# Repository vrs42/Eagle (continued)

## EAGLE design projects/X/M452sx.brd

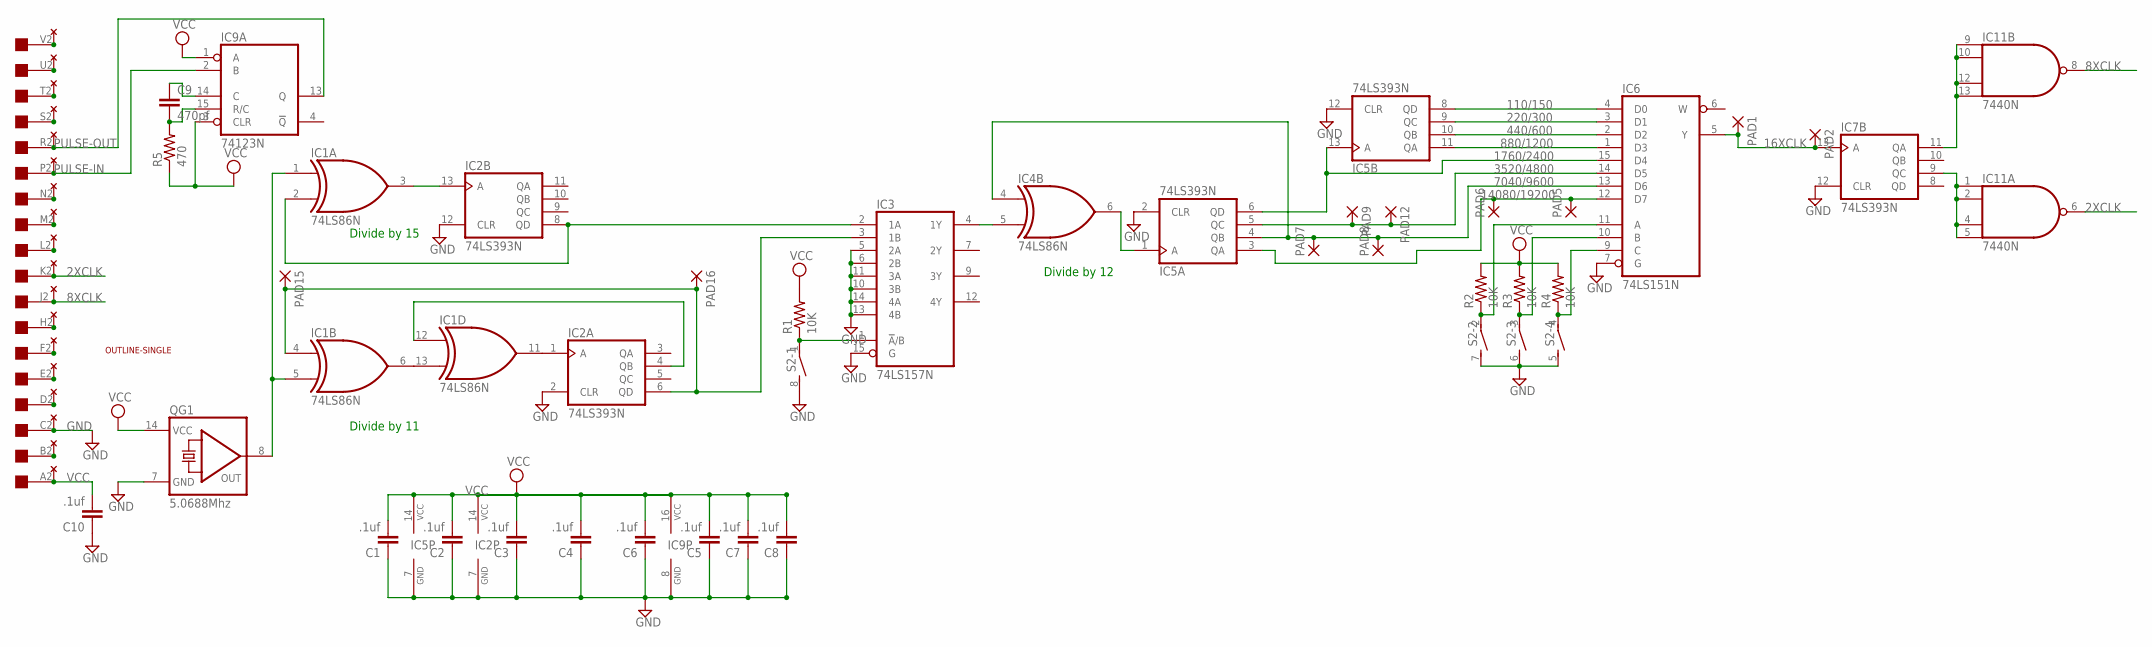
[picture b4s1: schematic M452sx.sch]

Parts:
C1, C2, C3, C4, C5, C6, C7, C8, C10: .1uf; C050-025X075
C9: 470pf; C050-025X075
IC1, IC4: 74LS86N; DIL14
IC2, IC5, IC7: 74LS393N; DIL14
IC3: 74LS157N; DIL16
IC6: 74LS151N; DIL16
IC9: 74123N; DIL16
IC11: 7440N; DIL14
PAD1, PAD2, PAD5, PAD6, PAD7, PAD8, PAD9, PAD12, PAD15, PAD16: 1,6/0,8
QG1: 5.0688Mhz; DIL14S
R1, R2, R3, R4: 10K; 0204/7
R5: 470; 0204/7
S2: DIP04S
U$2: EDGE-1; EDGE-CON1
U$3: THRU-HOLE1
U$4: OUTLINE-SINGLE; SINGLE

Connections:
2XCLK: IC11.6 (O), U$2.K2, U$3.K2
8XCLK: IC11.8 (O), U$2.J2, U$3.J2
16XCLK: IC6.5 (Y), IC7.13 (A), PAD1.1, PAD2.1
110/150: IC5.8 (QD), IC6.4 (D0)
220/300: IC5.9 (QC), IC6.3 (D1)
440/600: IC5.10 (QB), IC6.2 (D2)
880/1200: IC5.11 (QA), IC6.1 (D3)
1760/2400: IC5.6 (QD), IC5.13 (A), IC6.15 (D4)
3520/4800: IC5.5 (QC), IC6.14 (D5), PAD9.1, PAD12.1
7040/9600: IC4.4 (I0), IC5.4 (QB), IC6.13 (D6), PAD7.1, PAD8.1
14080/19200: IC5.3 (QA), IC6.12 (D7), PAD5.1, PAD6.1
GND: C1.1, C2.1, C3.1, C4.1, C5.1, C6.1, C7.1, C8.1, C10.1, IC1.7 (GND), IC2.2 (CLR), IC2.7 (GND), IC2.12 (CLR), IC3.5 (2A), IC3.6 (2B), IC3.8 (GND), IC3.10 (3B), IC3.11 (3A), IC3.13 (4B), IC3.14 (4A), IC3.15 (G), IC4.7 (GND), IC5.2 (CLR), IC5.7 (GND), IC5.12 (CLR), IC6.7 (G), IC6.8 (GND), IC7.7 (GND), IC7.12 (CLR), IC9.8 (GND), IC11.7 (GND), QG1.7 (GND), S2.5 (2), S2.6 (2), S2.7 (2), S2.8 (2), U$2.C2, U$3.C2
unnamed: IC1.1 (I0), IC1.5 (I1), QG1.8 (OUT)
unnamed: IC1.2 (I1), IC2.8 (QD), IC3.2 (1A)
unnamed: IC1.4 (I0), IC2.6 (QD), IC3.3 (1B), PAD15.1, PAD16.1
unnamed: U$2.V2, U$3.V2
unnamed: U$2.U2, U$3.U2
unnamed: IC1.3 (O), IC2.13 (A)
unnamed: IC1.11 (O), IC2.1 (A)
unnamed: IC6.11 (A), R2.1, S2.2 (1)
unnamed: IC3.4 (1Y), IC4.5 (I1)
unnamed: IC7.9 (QC), IC11.1 (I0), IC11.2 (I1), IC11.4 (I2), IC11.5 (I3)
unnamed: IC4.6 (O), IC5.1 (A)
unnamed: IC7.11 (QA), IC11.9 (I0), IC11.10 (I1), IC11.12 (I2), IC11.13 (I3)
unnamed: IC6.10 (B), R3.1, S2.3 (1)
unnamed: IC6.9 (C), R4.1, S2.4 (1)
unnamed: IC1.6 (O), IC1.13 (I1)
unnamed: U$2.T2, U$3.T2
unnamed: IC3.1 (!A!/B), R1.1, S2.1
unnamed: U$2.S2, U$3.S2
unnamed: IC1.12 (I0), IC2.4 (QB)
unnamed: U$2.N2, U$3.N2
unnamed: C9.2, IC9.15 (R/C), R5.2
unnamed: C9.1, IC9.14 (C)
unnamed: U$2.M2, U$3.M2
unnamed: U$2.L2, U$3.L2
unnamed: U$2.H2, U$3.H2
unnamed: U$2.F2, U$3.F2
unnamed: U$2.E2, U$3.E2
unnamed: U$2.D2, U$3.D2
unnamed: U$2.B2, U$3.B2
PULSE-IN: IC9.2 (B), U$2.P2, U$3.P2
PULSE-OUT: IC9.13 (Q), U$2.R2, U$3.R2
VCC: C1.2, C2.2, C3.2, C4.2, C5.2, C6.2, C7.2, C8.2, C10.2, IC1.14 (VCC), IC2.14 (VCC), IC3.16 (VCC), IC4.14 (VCC), IC5.14 (VCC), IC6.16 (VCC), IC7.14 (VCC), IC9.1 (A), IC9.3 (CLR), IC9.16 (VCC), IC11.14 (VCC), QG1.14 (VCC), R1.2, R2.2, R3.2, R4.2, R5.1, U$2.A2, U$3.A2

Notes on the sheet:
Divide by 11
Divide by 15
Divide by 12

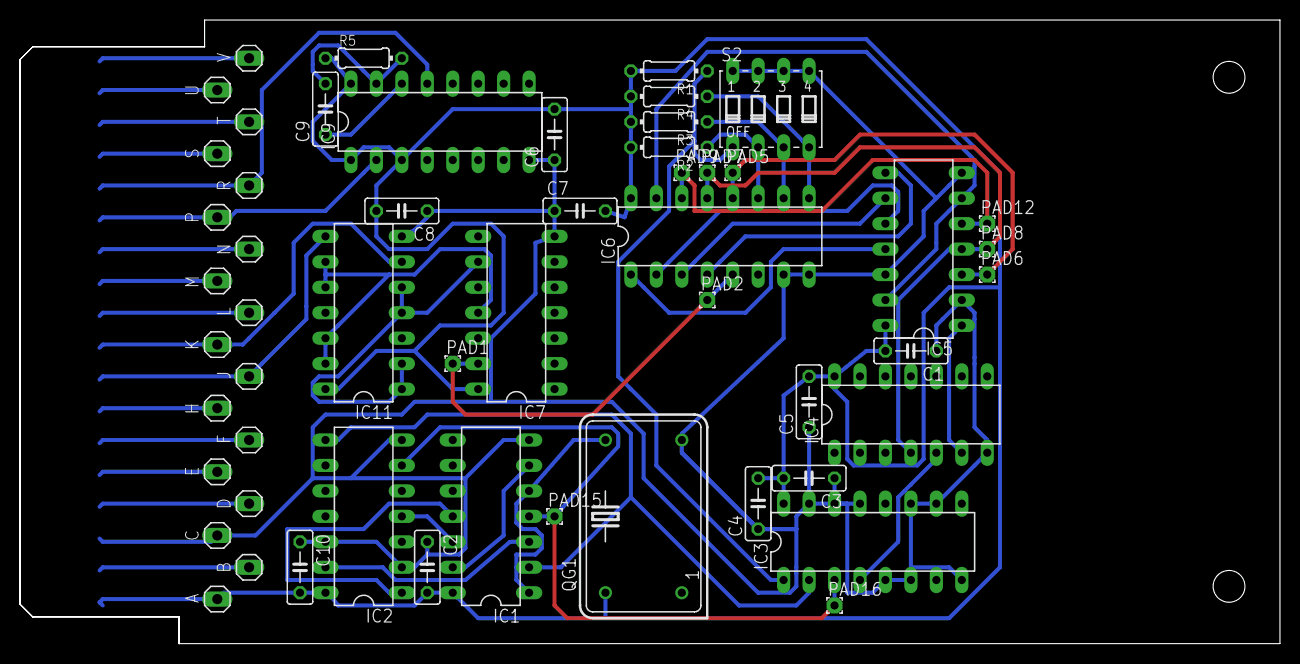
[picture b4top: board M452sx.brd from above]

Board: 2 copper layers, 125.7 x 62.2 mm, 39 parts (0 on the bottom side), 44 nets.

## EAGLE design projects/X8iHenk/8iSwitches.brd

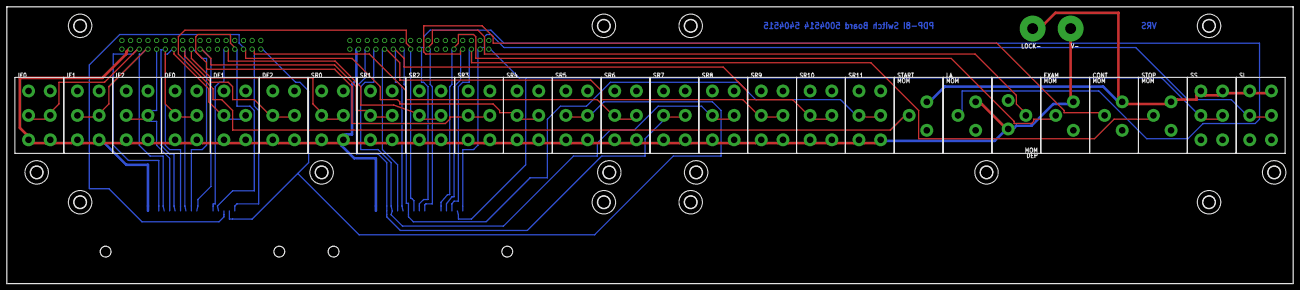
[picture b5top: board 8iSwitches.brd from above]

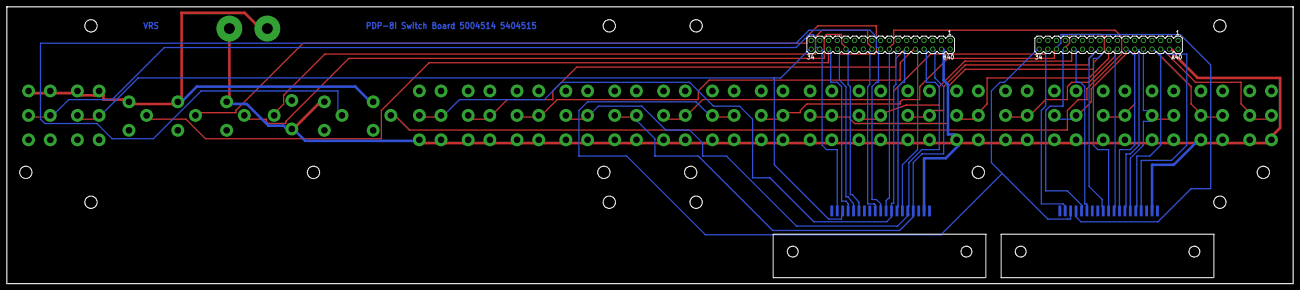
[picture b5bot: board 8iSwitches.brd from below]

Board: 2 copper layers, 376.2 x 81.0 mm, 48 parts (6 on the bottom side), 28 nets.

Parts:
A40: MA17-2
B40: MA17-2
CONT: SPDT8I
DEP: SPDT8I
DF0, DF1, DF2: DPDT8I
EXAM: SPDT8I
FLEXA: FLEX19
FLEXB: FLEX19
IF0, IF1, IF2: DPDT8I
LA: SPDT8I
LOCK-: LUG; SPADELUG
SI: DPDT8I
SR0, SR1, SR2, SR3, SR4, SR5, SR6, SR7, SR8, SR9, SR10, SR11: DPDT8I
SS: DPDT8I
START: SPDT8I
STOP: SPDT8I
U$1, U$2, U$3, U$4, U$5, U$6, U$7, U$10, U$11, U$12, U$13, U$14, U$15, U$16: 3,6
U$17, U$18: STRAIN-RELIEF
V-: LUG; SPADELUG

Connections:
CONT: B40.28, CONT.A2, FLEXB.5
DEP: B40.20, DEP.A2, FLEXB.9
DF0: A40.6, FLEXA.16, IF0.L2, IF0.R2
DF1: A40.8, FLEXA.15, IF1.L2, IF1.R2
DF2: A40.10, FLEXA.14, IF2.L2, IF2.R2
EXAM: B40.26, EXAM.A2, FLEXB.6
IF0: A40.12, DF0.L2, DF0.R2, FLEXA.13
IF1: A40.14, DF1.L2, DF1.R2, FLEXA.12
IF2: A40.16, DF2.L2, DF2.R2, FLEXA.11
LA: B40.18, FLEXB.10, LA.A2
LOCK-: CONT.A1, LOCK-.1, SI.L1, SI.R1, SS.L1, SS.R1, START.A1, STOP.A1
SI: B40.32, FLEXB.2, SI.L2, SI.R2
SR0: A40.18, FLEXA.10, SR0.L2, SR0.R2
SR1: A40.20, FLEXA.9, SR1.L2, SR1.R2
SR2: A40.26, FLEXA.6, SR2.L2, SR2.R2
SR3: A40.28, FLEXA.5, SR3.L2, SR3.R2
SR4: A40.30, FLEXA.4, SR4.L2, SR4.R2
SR5: A40.34, FLEXA.3, SR5.L2, SR5.R2
SR6: A40.32, FLEXA.2, SR6.L2, SR6.R2
SR7: B40.6, FLEXB.16, SR7.L2, SR7.R2
SR8: B40.8, FLEXB.15, SR8.L2, SR8.R2
SR9: B40.10, FLEXB.14, SR9.L2, SR9.R2
SR10: B40.12, FLEXB.13, SR10.L2, SR10.R2
SR11: B40.14, FLEXB.12, SR11.L2, SR11.R2
SS: B40.34, FLEXB.3, SS.L2, SS.R2
START: B40.16, FLEXB.11, START.A2
STOP: B40.30, FLEXB.4, STOP.A2
V-: A40.4, B40.4, DEP.A1, DF0.L3, DF0.R3, DF1.L3, DF1.R3, DF2.L3, DF2.R3, EXAM.A1, FLEXA.18, FLEXB.18, IF0.L3, IF0.R3, IF1.L3, IF1.R3, IF2.L3, IF2.R3, LA.A1, SR0.L3, SR0.R3, SR1.L3, SR1.R3, SR2.L3, SR2.R3, SR3.L3, SR3.R3, SR4.L3, SR4.R3, SR5.L3, SR5.R3, SR6.L3, SR6.R3, SR7.L3, SR7.R3, SR8.L3, SR8.R3, SR9.L3, SR9.R3, SR10.L3, SR10.R3, SR11.L3, SR11.R3, V-.1

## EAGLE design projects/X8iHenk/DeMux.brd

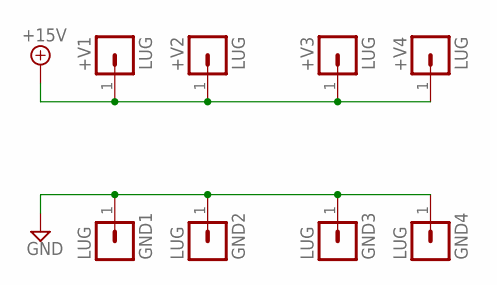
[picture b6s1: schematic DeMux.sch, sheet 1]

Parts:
+V1, +V2, +V3, +V4: LUG; SPADELUG
GND1, GND2, GND3, GND4: LUG; SPADELUG

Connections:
+15V: +V1.1, +V2.1, +V3.1, +V4.1
GND: GND1.1, GND2.1, GND3.1, GND4.1; also elsewhere on the board

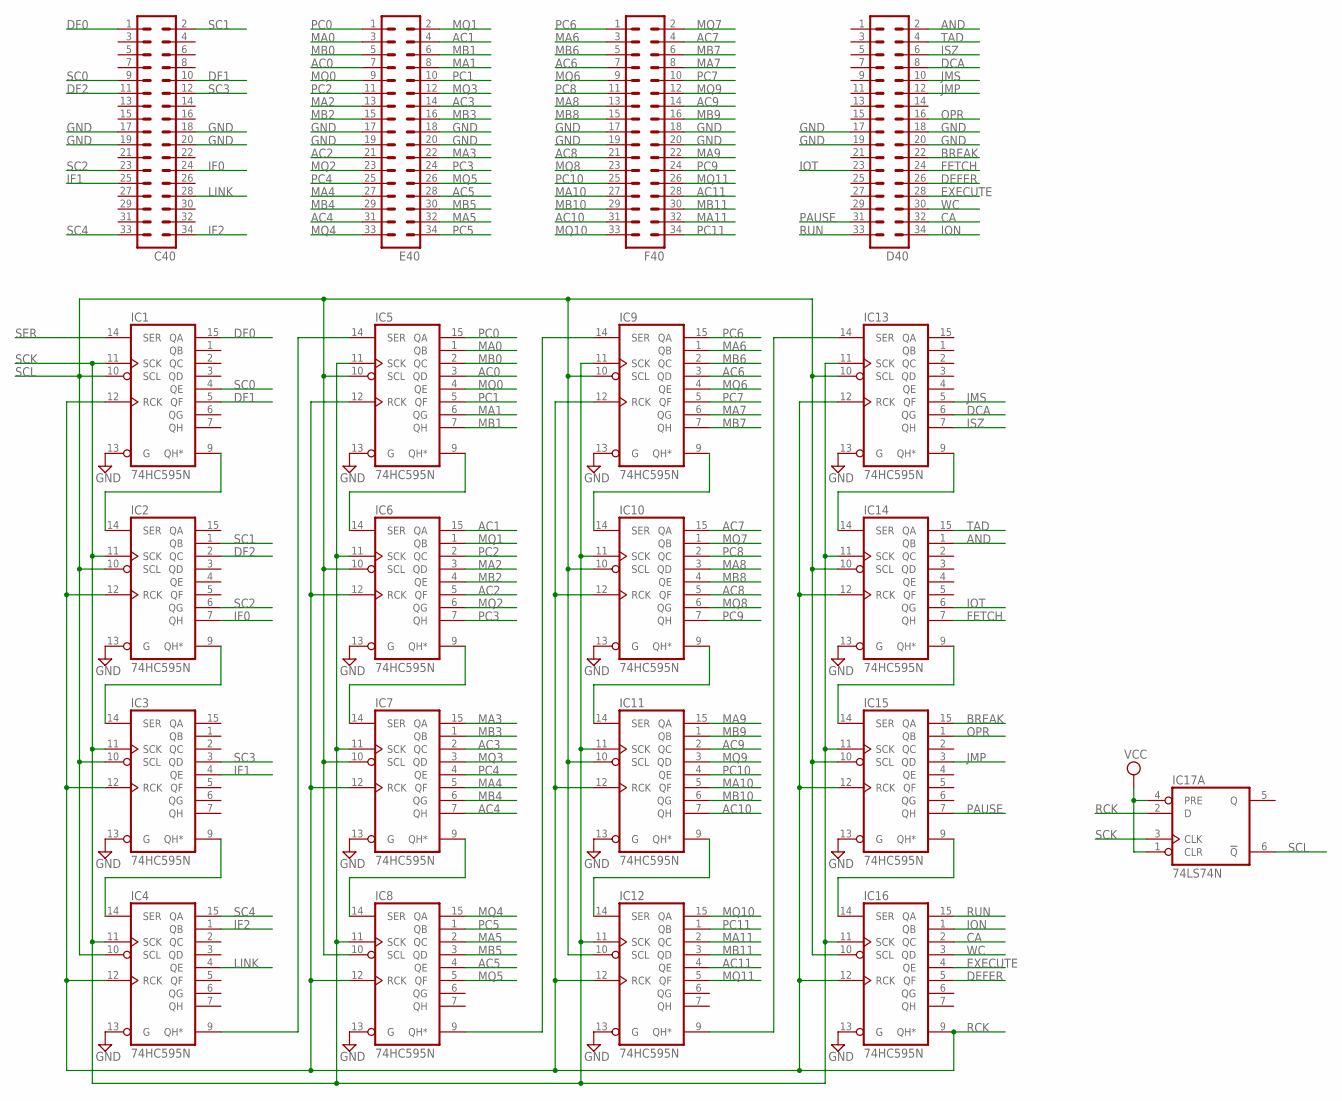
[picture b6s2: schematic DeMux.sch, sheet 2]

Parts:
C40: MA17-2
D40: MA17-2
E40: MA17-2
F40: MA17-2
IC1, IC2, IC3, IC4, IC5, IC6, IC7, IC8, IC9, IC10, IC11, IC12, IC13, IC14, IC15, IC16: 74HC595N; DIL16
IC17: 74LS74N; DIL14

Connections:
AC0: E40.7, IC5.3 (QD)
AC1: E40.4, IC6.15 (QA)
AC2: E40.21, IC6.5 (QF)
AC3: E40.14, IC7.2 (QC)
AC4: E40.31, IC7.7 (QH)
AC5: E40.28, IC8.4 (QE)
AC6: F40.7, IC9.3 (QD)
AC7: F40.4, IC10.15 (QA)
AC8: F40.21, IC10.5 (QF)
AC9: F40.14, IC11.2 (QC)
AC10: F40.31, IC11.7 (QH)
AC11: F40.28, IC12.4 (QE)
AND: D40.2, IC14.1 (QB)
BREAK: D40.22, IC15.15 (QA)
CA: D40.32, IC16.2 (QC)
DCA: D40.8, IC13.6 (QG)
DEFER: D40.26, IC16.5 (QF)
DF0: C40.1, IC1.15 (QA)
DF1: C40.10, IC1.5 (QF)
DF2: C40.11, IC2.2 (QC)
EXECUTE: D40.28, IC16.4 (QE)
FETCH: D40.24, IC14.7 (QH)
GND: C40.17, C40.18, C40.19, C40.20, D40.17, D40.18, D40.19, D40.20, E40.17, E40.18, E40.19, E40.20, F40.17, F40.18, F40.19, F40.20, IC1.8 (GND), IC1.13 (G), IC2.8 (GND), IC2.13 (G), IC3.8 (GND), IC3.13 (G), IC4.8 (GND), IC4.13 (G), IC5.8 (GND), IC5.13 (G), IC6.8 (GND), IC6.13 (G), IC7.8 (GND), IC7.13 (G), IC8.8 (GND), IC8.13 (G), IC9.8 (GND), IC9.13 (G), IC10.8 (GND), IC10.13 (G), IC11.8 (GND), IC11.13 (G), IC12.8 (GND), IC12.13 (G), IC13.8 (GND), IC13.13 (G), IC14.8 (GND), IC14.13 (G), IC15.8 (GND), IC15.13 (G), IC16.8 (GND), IC16.13 (G), IC17.7 (GND); also elsewhere on the board
IF0: C40.24, IC2.7 (QH)
IF1: C40.25, IC3.4 (QE)
IF2: C40.34, IC4.1 (QB)
ION: D40.34, IC16.1 (QB)
IOT: D40.23, IC14.6 (QG)
ISZ: D40.6, IC13.7 (QH)
JMP: D40.12, IC15.3 (QD)
JMS: D40.10, IC13.5 (QF)
LINK: C40.28, IC4.4 (QE)
MA0: E40.3, IC5.1 (QB)
MA1: E40.8, IC5.6 (QG)
MA2: E40.13, IC6.3 (QD)
MA3: E40.22, IC7.15 (QA)
MA4: E40.27, IC7.5 (QF)
MA5: E40.32, IC8.2 (QC)
MA6: F40.3, IC9.1 (QB)
MA7: F40.8, IC9.6 (QG)
MA8: F40.13, IC10.3 (QD)
MA9: F40.22, IC11.15 (QA)
MA10: F40.27, IC11.5 (QF)
MA11: F40.32, IC12.2 (QC)
MB0: E40.5, IC5.2 (QC)
MB1: E40.6, IC5.7 (QH)
MB2: E40.15, IC6.4 (QE)
MB3: E40.16, IC7.1 (QB)
MB4: E40.29, IC7.6 (QG)
MB5: E40.30, IC8.3 (QD)
MB6: F40.5, IC9.2 (QC)
MB7: F40.6, IC9.7 (QH)
MB8: F40.15, IC10.4 (QE)
MB9: F40.16, IC11.1 (QB)
MB10: F40.29, IC11.6 (QG)
MB11: F40.30, IC12.3 (QD)
MQ0: E40.9, IC5.4 (QE)
MQ1: E40.2, IC6.1 (QB)
MQ2: E40.23, IC6.6 (QG)
MQ3: E40.12, IC7.3 (QD)
MQ4: E40.33, IC8.15 (QA)
MQ5: E40.26, IC8.5 (QF)
MQ6: F40.9, IC9.4 (QE)
MQ7: F40.2, IC10.1 (QB)
MQ8: F40.23, IC10.6 (QG)
MQ9: F40.12, IC11.3 (QD)
MQ10: F40.33, IC12.15 (QA)
MQ11: F40.26, IC12.5 (QF)
unnamed: IC5.9 (QH*), IC6.14 (SER)
unnamed: IC1.9 (QH*), IC2.14 (SER)
unnamed: IC2.9 (QH*), IC3.14 (SER)
unnamed: IC3.9 (QH*), IC4.14 (SER)
unnamed: IC7.9 (QH*), IC8.14 (SER)
unnamed: IC6.9 (QH*), IC7.14 (SER)
unnamed: IC11.9 (QH*), IC12.14 (SER)
unnamed: IC10.9 (QH*), IC11.14 (SER)
unnamed: IC14.9 (QH*), IC15.14 (SER)
unnamed: IC15.9 (QH*), IC16.14 (SER)
unnamed: IC9.9 (QH*), IC10.14 (SER)
unnamed: IC13.9 (QH*), IC14.14 (SER)
unnamed: IC4.9 (QH*), IC5.14 (SER)
unnamed: IC8.9 (QH*), IC9.14 (SER)
unnamed: IC12.9 (QH*), IC13.14 (SER)
OPR: D40.16, IC15.1 (QB)
PAUSE: D40.31, IC15.7 (QH)
PC0: E40.1, IC5.15 (QA)
PC1: E40.10, IC5.5 (QF)
PC2: E40.11, IC6.2 (QC)
PC3: E40.24, IC6.7 (QH)
PC4: E40.25, IC7.4 (QE)
PC5: E40.34, IC8.1 (QB)
PC6: F40.1, IC9.15 (QA)
PC7: F40.10, IC9.5 (QF)
PC8: F40.11, IC10.2 (QC)
PC9: F40.24, IC10.7 (QH)
PC10: F40.25, IC11.4 (QE)
PC11: F40.34, IC12.1 (QB)
RCK: IC1.12 (RCK), IC2.12 (RCK), IC3.12 (RCK), IC4.12 (RCK), IC5.12 (RCK), IC6.12 (RCK), IC7.12 (RCK), IC8.12 (RCK), IC9.12 (RCK), IC10.12 (RCK), IC11.12 (RCK), IC12.12 (RCK), IC13.12 (RCK), IC14.12 (RCK), IC15.12 (RCK), IC16.9 (QH*), IC16.12 (RCK), IC17.2 (D)
RUN: D40.33, IC16.15 (QA)
SC0: C40.9, IC1.4 (QE)
SC1: C40.2, IC2.1 (QB)
SC2: C40.23, IC2.6 (QG)
SC3: C40.12, IC3.3 (QD)
SC4: C40.33, IC4.15 (QA)
SCK: IC1.11 (SCK), IC2.11 (SCK), IC3.11 (SCK), IC4.11 (SCK), IC5.11 (SCK), IC6.11 (SCK), IC7.11 (SCK), IC8.11 (SCK), IC9.11 (SCK), IC10.11 (SCK), IC11.11 (SCK), IC12.11 (SCK), IC13.11 (SCK), IC14.11 (SCK), IC15.11 (SCK), IC16.11 (SCK), IC17.3 (CLK)
SCL: IC1.10 (SCL), IC2.10 (SCL), IC3.10 (SCL), IC4.10 (SCL), IC5.10 (SCL), IC6.10 (SCL), IC7.10 (SCL), IC8.10 (SCL), IC9.10 (SCL), IC10.10 (SCL), IC11.10 (SCL), IC12.10 (SCL), IC13.10 (SCL), IC14.10 (SCL), IC15.10 (SCL), IC16.10 (SCL), IC17.6 (!Q)
SER: IC1.14 (SER)
TAD: D40.4, IC14.15 (QA)
VCC: IC1.16 (VCC), IC2.16 (VCC), IC3.16 (VCC), IC4.16 (VCC), IC5.16 (VCC), IC6.16 (VCC), IC7.16 (VCC), IC8.16 (VCC), IC9.16 (VCC), IC10.16 (VCC), IC11.16 (VCC), IC12.16 (VCC), IC13.16 (VCC), IC14.16 (VCC), IC15.16 (VCC), IC16.16 (VCC), IC17.1 (CLR), IC17.4 (PRE), IC17.14 (VCC)
WC: D40.30, IC16.3 (QD)

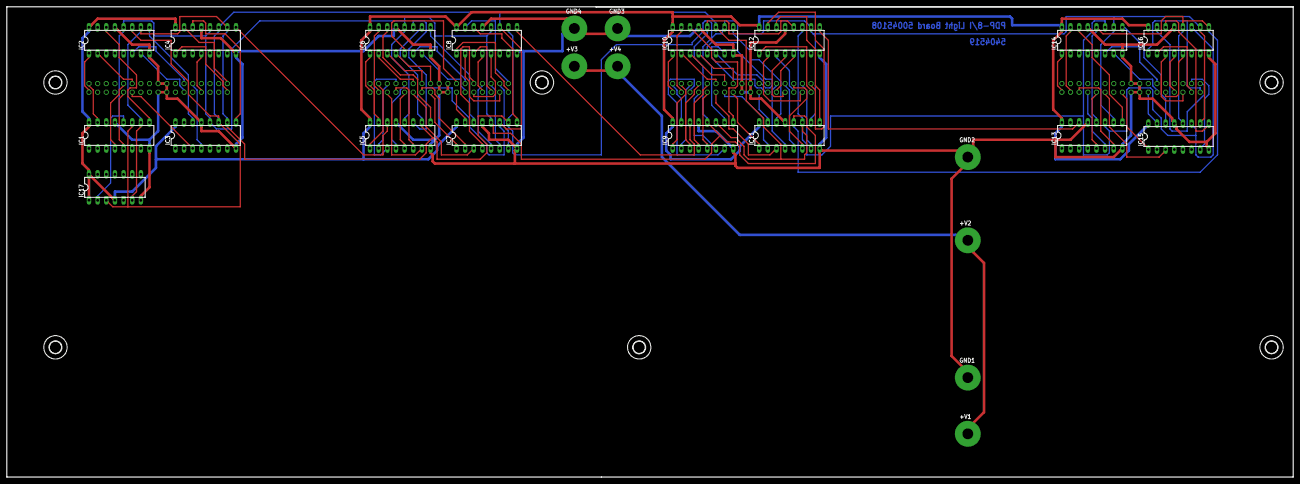
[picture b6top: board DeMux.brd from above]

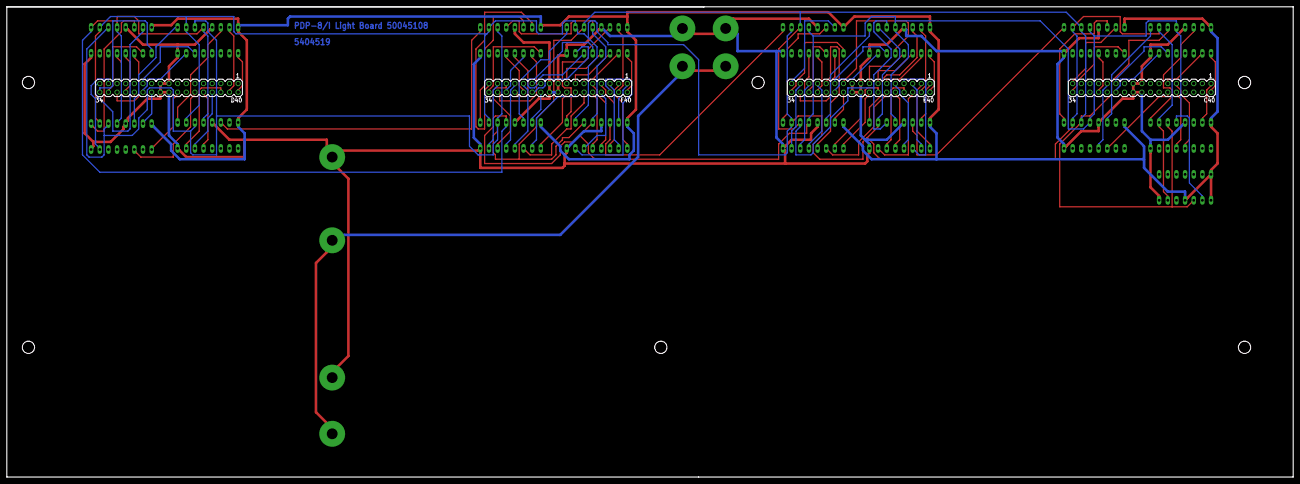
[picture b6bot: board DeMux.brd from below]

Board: 2 copper layers, 377.8 x 138.1 mm, 35 parts (4 on the bottom side), 110 nets.

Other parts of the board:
U$5, U$6, U$7, U$8, U$9, U$11: 3,6

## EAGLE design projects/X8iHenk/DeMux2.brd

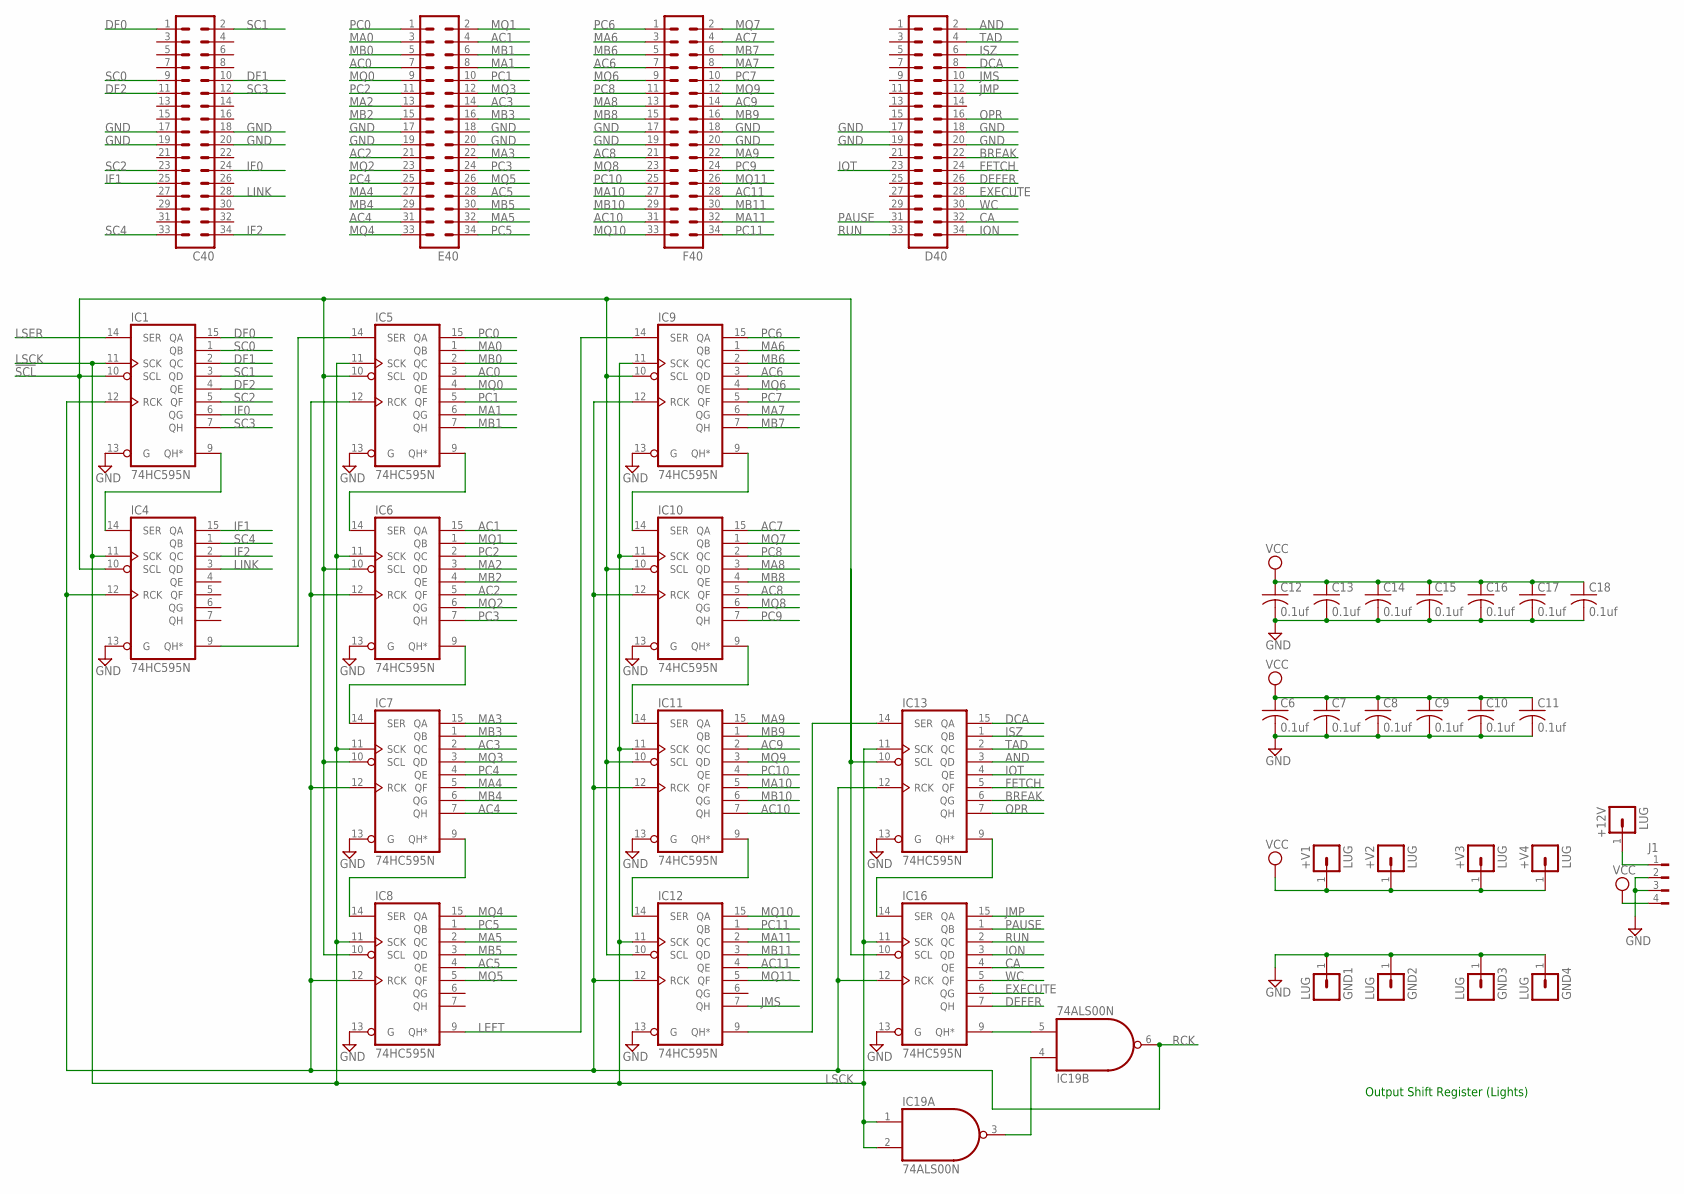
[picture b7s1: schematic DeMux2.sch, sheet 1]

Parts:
+12V: LUG; SPADELUG
+V1, +V2, +V3, +V4: LUG; SPADELUG
C6, C7, C8, C9, C10, C11, C12, C13, C14, C15, C16, C17, C18: 0.1uf; C050-025X075
C40: MA17-2
D40: MA17-2
E40: MA17-2
F40: MA17-2
GND1, GND2, GND3, GND4: LUG; SPADELUG
IC1, IC4, IC5, IC6, IC7, IC8, IC9, IC10, IC11, IC12, IC13, IC16: 74HC595N; DIL16
IC19: 74ALS00N; DIL14
J1: FLOPPY-4

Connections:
!SCL: IC1.10 (SCL), IC4.10 (SCL), IC5.10 (SCL), IC6.10 (SCL), IC7.10 (SCL), IC8.10 (SCL), IC9.10 (SCL), IC10.10 (SCL), IC11.10 (SCL), IC12.10 (SCL), IC13.10 (SCL), IC16.10 (SCL); also elsewhere on the board
+12V: +12V.1, J1.1
AC0: E40.7, IC5.3 (QD)
AC1: E40.4, IC6.15 (QA)
AC2: E40.21, IC6.5 (QF)
AC3: E40.14, IC7.2 (QC)
AC4: E40.31, IC7.7 (QH)
AC5: E40.28, IC8.4 (QE)
AC6: F40.7, IC9.3 (QD)
AC7: F40.4, IC10.15 (QA)
AC8: F40.21, IC10.5 (QF)
AC9: F40.14, IC11.2 (QC)
AC10: F40.31, IC11.7 (QH)
AC11: F40.28, IC12.4 (QE)
AND: D40.2, IC13.3 (QD)
BREAK: D40.22, IC13.6 (QG)
CA: D40.32, IC16.4 (QE)
DCA: D40.8, IC13.15 (QA)
DEFER: D40.26, IC16.7 (QH)
DF0: C40.1, IC1.15 (QA)
DF1: C40.10, IC1.2 (QC)
DF2: C40.11, IC1.4 (QE)
EXECUTE: D40.28, IC16.6 (QG)
FETCH: D40.24, IC13.5 (QF)
GND: C6.2, C7.2, C8.2, C9.2, C10.2, C11.2, C12.2, C13.2, C14.2, C15.2, C16.2, C17.2, C18.2, C40.17, C40.18, C40.19, C40.20, D40.17, D40.18, D40.19, D40.20, E40.17, E40.18, E40.19, E40.20, F40.17, F40.18, F40.19, F40.20, GND1.1, GND2.1, GND3.1, GND4.1, IC1.8 (GND), IC1.13 (G), IC4.8 (GND), IC4.13 (G), IC5.8 (GND), IC5.13 (G), IC6.8 (GND), IC6.13 (G), IC7.8 (GND), IC7.13 (G), IC8.8 (GND), IC8.13 (G), IC9.8 (GND), IC9.13 (G), IC10.8 (GND), IC10.13 (G), IC11.8 (GND), IC11.13 (G), IC12.8 (GND), IC12.13 (G), IC13.8 (GND), IC13.13 (G), IC16.8 (GND), IC16.13 (G), IC19.7 (GND), J1.2, J1.3; also elsewhere on the board
IF0: C40.24, IC1.6 (QG)
IF1: C40.25, IC4.15 (QA)
IF2: C40.34, IC4.2 (QC)
ION: D40.34, IC16.3 (QD)
IOT: D40.23, IC13.4 (QE)
ISZ: D40.6, IC13.1 (QB)
JMP: D40.12, IC16.15 (QA)
JMS: D40.10, IC12.7 (QH)
LEFT: IC8.9 (QH*), IC9.14 (SER); also elsewhere on the board
LINK: C40.28, IC4.3 (QD)
LSCK: IC1.11 (SCK), IC4.11 (SCK), IC5.11 (SCK), IC6.11 (SCK), IC7.11 (SCK), IC8.11 (SCK), IC9.11 (SCK), IC10.11 (SCK), IC11.11 (SCK), IC12.11 (SCK), IC13.11 (SCK), IC16.11 (SCK), IC19.1 (I0), IC19.2 (I1); also elsewhere on the board
LSER: IC1.14 (SER); also elsewhere on the board
MA0: E40.3, IC5.1 (QB)
MA1: E40.8, IC5.6 (QG)
MA2: E40.13, IC6.3 (QD)
MA3: E40.22, IC7.15 (QA)
MA4: E40.27, IC7.5 (QF)
MA5: E40.32, IC8.2 (QC)
MA6: F40.3, IC9.1 (QB)
MA7: F40.8, IC9.6 (QG)
MA8: F40.13, IC10.3 (QD)
MA9: F40.22, IC11.15 (QA)
MA10: F40.27, IC11.5 (QF)
MA11: F40.32, IC12.2 (QC)
MB0: E40.5, IC5.2 (QC)
MB1: E40.6, IC5.7 (QH)
MB2: E40.15, IC6.4 (QE)
MB3: E40.16, IC7.1 (QB)
MB4: E40.29, IC7.6 (QG)
MB5: E40.30, IC8.3 (QD)
MB6: F40.5, IC9.2 (QC)
MB7: F40.6, IC9.7 (QH)
MB8: F40.15, IC10.4 (QE)
MB9: F40.16, IC11.1 (QB)
MB10: F40.29, IC11.6 (QG)
MB11: F40.30, IC12.3 (QD)
MQ0: E40.9, IC5.4 (QE)
MQ1: E40.2, IC6.1 (QB)
MQ2: E40.23, IC6.6 (QG)
MQ3: E40.12, IC7.3 (QD)
MQ4: E40.33, IC8.15 (QA)
MQ5: E40.26, IC8.5 (QF)
MQ6: F40.9, IC9.4 (QE)
MQ7: F40.2, IC10.1 (QB)
MQ8: F40.23, IC10.6 (QG)
MQ9: F40.12, IC11.3 (QD)
MQ10: F40.33, IC12.15 (QA)
MQ11: F40.26, IC12.5 (QF)
unnamed: IC5.9 (QH*), IC6.14 (SER)
unnamed: IC1.9 (QH*), IC4.14 (SER)
unnamed: IC7.9 (QH*), IC8.14 (SER)
unnamed: IC6.9 (QH*), IC7.14 (SER)
unnamed: IC11.9 (QH*), IC12.14 (SER)
unnamed: IC10.9 (QH*), IC11.14 (SER)
unnamed: IC13.9 (QH*), IC16.14 (SER)
unnamed: IC9.9 (QH*), IC10.14 (SER)
unnamed: IC4.9 (QH*), IC5.14 (SER)
unnamed: IC16.9 (QH*), IC19.5 (I1)
unnamed: IC12.9 (QH*), IC13.14 (SER)
unnamed: IC19.3 (O), IC19.4 (I0)
OPR: D40.16, IC13.7 (QH)
PAUSE: D40.31, IC16.1 (QB)
PC0: E40.1, IC5.15 (QA)
PC1: E40.10, IC5.5 (QF)
PC2: E40.11, IC6.2 (QC)
PC3: E40.24, IC6.7 (QH)
PC4: E40.25, IC7.4 (QE)
PC5: E40.34, IC8.1 (QB)
PC6: F40.1, IC9.15 (QA)
PC7: F40.10, IC9.5 (QF)
PC8: F40.11, IC10.2 (QC)
PC9: F40.24, IC10.7 (QH)
PC10: F40.25, IC11.4 (QE)
PC11: F40.34, IC12.1 (QB)
RCK: IC1.12 (RCK), IC4.12 (RCK), IC5.12 (RCK), IC6.12 (RCK), IC7.12 (RCK), IC8.12 (RCK), IC9.12 (RCK), IC10.12 (RCK), IC11.12 (RCK), IC12.12 (RCK), IC13.12 (RCK), IC16.12 (RCK), IC19.6 (O); also elsewhere on the board
RUN: D40.33, IC16.2 (QC)
SC0: C40.9, IC1.1 (QB)
SC1: C40.2, IC1.3 (QD)
SC2: C40.23, IC1.5 (QF)
SC3: C40.12, IC1.7 (QH)
SC4: C40.33, IC4.1 (QB)
TAD: D40.4, IC13.2 (QC)
VCC: +V1.1, +V2.1, +V3.1, +V4.1, C6.1, C7.1, C8.1, C9.1, C10.1, C11.1, C12.1, C13.1, C14.1, C15.1, C16.1, C17.1, C18.1, IC1.16 (VCC), IC4.16 (VCC), IC5.16 (VCC), IC6.16 (VCC), IC7.16 (VCC), IC8.16 (VCC), IC9.16 (VCC), IC10.16 (VCC), IC11.16 (VCC), IC12.16 (VCC), IC13.16 (VCC), IC16.16 (VCC), IC19.14 (VCC), J1.4; also elsewhere on the board
WC: D40.30, IC16.5 (QF)

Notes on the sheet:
Output Shift Register (Lights)

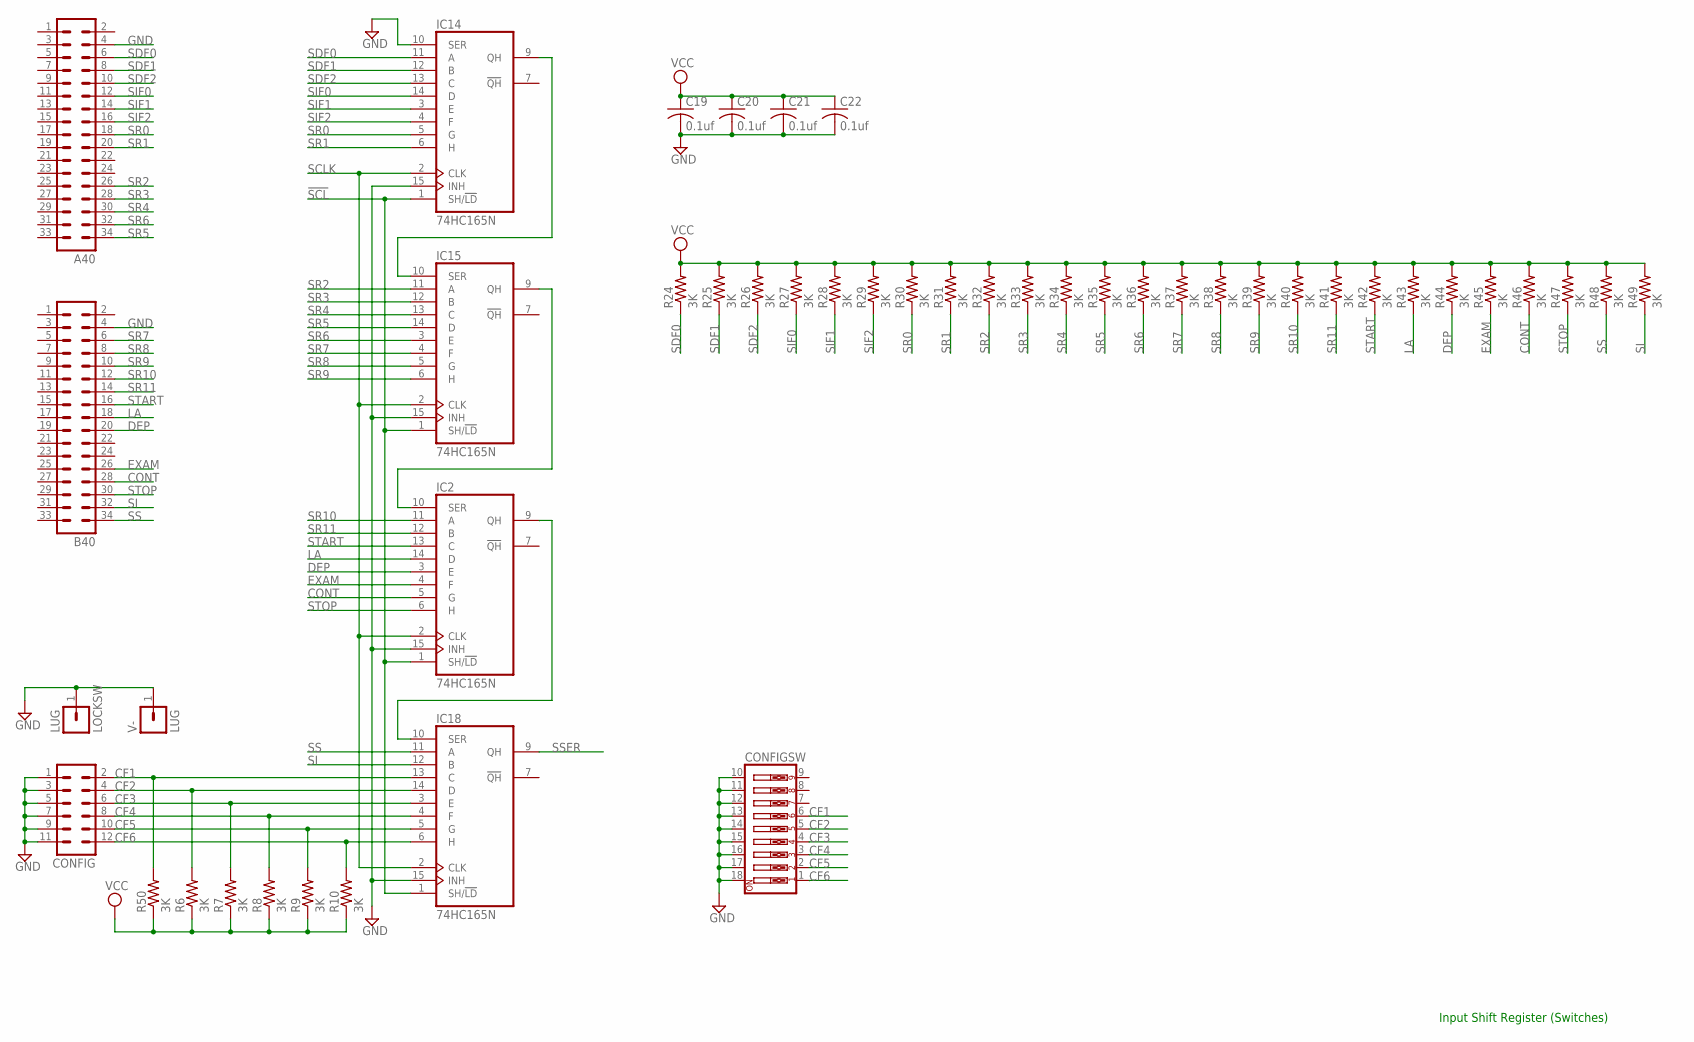
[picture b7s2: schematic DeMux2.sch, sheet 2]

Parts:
A40: MA17-2
B40: MA17-2
C19, C20, C21, C22: 0.1uf; C050-025X075
CONFIG: MA06-2
CONFIGSW: SW_DIP-9; EDG-09
IC2, IC14, IC15, IC18: 74HC165N; DIL16
LOCKSW: LUG; SPADELUG
R6, R7, R8, R9, R10, R24, R25, R26, R27, R28, R29, R30, R31, R32, R33, R34, R35, R36, R37, R38, R39, R40, R41, R42, R43, R44, R45, R46, R47, R48, R49, R50: 3K; 0207/10
V-: LUG; SPADELUG

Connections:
!SCL: IC2.1 (SH/!LD), IC14.1 (SH/!LD), IC15.1 (SH/!LD), IC18.1 (SH/!LD); also elsewhere on the board
CF1: CONFIG.2, CONFIGSW.6, IC18.13 (C), R50.2
CF2: CONFIG.4, CONFIGSW.5, IC18.14 (D), R6.2
CF3: CONFIG.6, CONFIGSW.4, IC18.3 (E), R7.2
CF4: CONFIG.8, CONFIGSW.3, IC18.4 (F), R8.2
CF5: CONFIG.10, CONFIGSW.2, IC18.5 (G), R9.2
CF6: CONFIG.12, CONFIGSW.1, IC18.6 (H), R10.2
CONT: B40.28, IC2.5 (G), R46.1
DEP: B40.20, IC2.3 (E), R44.1
EXAM: B40.26, IC2.4 (F), R45.1
GND: A40.4, B40.4, C19.2, C20.2, C21.2, C22.2, CONFIG.1, CONFIG.3, CONFIG.5, CONFIG.7, CONFIG.9, CONFIG.11, CONFIGSW.10, CONFIGSW.11, CONFIGSW.12, CONFIGSW.13, CONFIGSW.14, CONFIGSW.15, CONFIGSW.16, CONFIGSW.17, CONFIGSW.18, IC2.8 (GND), IC2.15 (INH), IC14.8 (GND), IC14.10 (SER), IC14.15 (INH), IC15.8 (GND), IC15.15 (INH), IC18.8 (GND), IC18.15 (INH), LOCKSW.1, V-.1; also elsewhere on the board
LA: B40.18, IC2.14 (D), R43.1
unnamed: IC14.9 (QH), IC15.10 (SER)
unnamed: IC2.10 (SER), IC15.9 (QH)
unnamed: IC2.9 (QH), IC18.10 (SER)
SCLK: IC2.2 (CLK), IC14.2 (CLK), IC15.2 (CLK), IC18.2 (CLK); also elsewhere on the board
SDF0: A40.6, IC14.11 (A), R24.1
SDF1: A40.8, IC14.12 (B), R25.1
SDF2: A40.10, IC14.13 (C), R26.1
SI: B40.32, IC18.12 (B), R49.1
SIF0: A40.12, IC14.14 (D), R27.1
SIF1: A40.14, IC14.3 (E), R28.1
SIF2: A40.16, IC14.4 (F), R29.1
SR0: A40.18, IC14.5 (G), R30.1
SR1: A40.20, IC14.6 (H), R31.1
SR2: A40.26, IC15.11 (A), R32.1
SR3: A40.28, IC15.12 (B), R33.1
SR4: A40.30, IC15.13 (C), R34.1
SR5: A40.34, IC15.14 (D), R35.1
SR6: A40.32, IC15.3 (E), R36.1
SR7: B40.6, IC15.4 (F), R37.1
SR8: B40.8, IC15.5 (G), R38.1
SR9: B40.10, IC15.6 (H), R39.1
SR10: B40.12, IC2.11 (A), R40.1
SR11: B40.14, IC2.12 (B), R41.1
SS: B40.34, IC18.11 (A), R48.1
SSER: IC18.9 (QH); also elsewhere on the board
START: B40.16, IC2.13 (C), R42.1
STOP: B40.30, IC2.6 (H), R47.1
VCC: C19.1, C20.1, C21.1, C22.1, IC2.16 (VCC), IC14.16 (VCC), IC15.16 (VCC), IC18.16 (VCC), R6.1, R7.1, R8.1, R9.1, R10.1, R24.2, R25.2, R26.2, R27.2, R28.2, R29.2, R30.2, R31.2, R32.2, R33.2, R34.2, R35.2, R36.2, R37.2, R38.2, R39.2, R40.2, R41.2, R42.2, R43.2, R44.2, R45.2, R46.2, R47.2, R48.2, R49.2, R50.1; also elsewhere on the board

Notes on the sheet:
Input Shift Register (Switches)
